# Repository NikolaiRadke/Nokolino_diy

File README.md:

The ATtiny-based litte brother of Noko. This is the Repository for the **diy - Do It Yourself** version. Tiny and cute. And everyone is invited to **contribute**. Nokolino is for everyone. Are you looking for the new PCB version? Look here: [Nokolino_pcb](https://github.com/NikolaiRadke/Nokolino_pcb), or are you an owner of a kit? Look [here](http://github.com/NikolaiRadke/Nokolino).  

> [!NOTE]
> This Repository is not maintained anymore. 
  
What's new? See the [newsblog](https://github.com/NikolaiRadke/Nokolino_diy/tree/master/NEWS.md).   

Like his big brother **Noko**, the little Nokolino delights it's surroundings with cheeky comments. But unlike Noko he is more obstinate - no radio, no display, no frills. Instead of an Arduino he has a small **ATtiny** microcontroller, only an on-off switch and a big button. But he is small, can stay active for days and is, in contrast to his big brother, very easy to build.  
  
Another useful application option would be to use the hardware without the monster suit as a **music box** in an old used doll to bring it back to modern days, maybe with other sounds or songs.  

What does he to - technically? Whenever you press his button, he will laugh. And when he's just turned on, he says something random randomly every statistically 10 minutes. That's ist. Quiet a lot for a stuffed monster!  
  
**Nokolino** stands for **No**ra and Ni**ko**s monster - the appendix **lino** describes the small version.  
  
### Notes for non-German Nokolino makers  
  
Right now, the building wiki, the voice set and the manual are in German. I'll try to translate the wiki and the manual on day. Until then, feel free to ask me for translation, if you need help. **Contribute!** I need an English voice set and English text files. In addition, any other language is welcome, Nokolino is to be cosmopolitan!
  
### Prerequisites
  
Nokolino needs Arduino IDE 1.6.6 or newer (https://www.arduino.cc/en/Main/Software). Copy the folder `Nokolino_diy/src/Nokolino/` into your sketch folder and install ATtiny support. See [how to compile](https://github.com/NikolaiRadke/Nokolino_diy/tree/master/howto_compile) for further instructions. 
  
### Content

```
Nokolino_diy/
├── howto_compile/
|   Manual how compile the sketches in your Arduino IDE and precompiled sketched  
|   └── precompiled/
|       Precompiled hex files
|       ├── ATtiny45/
|       |   Version for the ATtiny45.
|       └── ATtiny85/
|           Version for the ATtiny85.
|
├── linux_uploader/
|   Tool for uploading MP3-files to the JQ6500.
|
├── manual/
|   Nokolino manual in PDF format and a template for a packaging design.
|   └── scribus/
|       Source documents for Scribus with all illustrations and fonts.
|
├── mp3/
|   Voice set for Nokolino/Nokolina in German. English needed? Contribute!
|   ├── female/
|   |   Female voice for Nokolina.
|   |   ├── mp3_16MBit/
|   |   |   Voice set for the 2MB-JQ6500.
|   |   └── mp3_32MBit/
|   |       Enhanced voice set for the 4MB-JQ6500. 
|   └── male/
|       Male voice for Nokolino.
|       ├── mp3_8MBit/
|       |   Low qualitiy files for the 1MB-JQ6500.
|       ├── mp3_16MBit/
|       |   Voice set for the 2MB-JQ6500.
|       └── mp3_32MBit/
|           Enhanched voice set for the 4MB-JQ6500.  
|
├── schematics/
|   The schematics for the Nokolino parts, the Nokolino sewing pattern and shopping list.
|   └── geda/
|       Source documents for gEDA.
|
└── src/
    ATtiny sketch
    └── Nokolino/
        One file, no libraries, no frills. Just Nokolino. 
```
### Let's get started!

Interested in Nokolino? Great! Let's start here: [German wiki](https://github.com/NikolaiRadke/Nokolino_diy/wiki).  
English wiki will follow. One day...

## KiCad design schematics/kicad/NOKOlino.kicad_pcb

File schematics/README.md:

# Schematics

### Technical schematics
* **Nokolino.png**:  
NOKOlino's main schematic. It was written with [gEDA](http://www.geda-project.org/).  
* **Nokolino_phototransistor.png**:  
Optional light sensor extension schematic.  

### Other manuals

* **Nokolino_Pattern.pdf**:
NOKOs sewing pattern. 
* **Nokolino_Einkaufsliste.pdf**:
Shopping list in German.

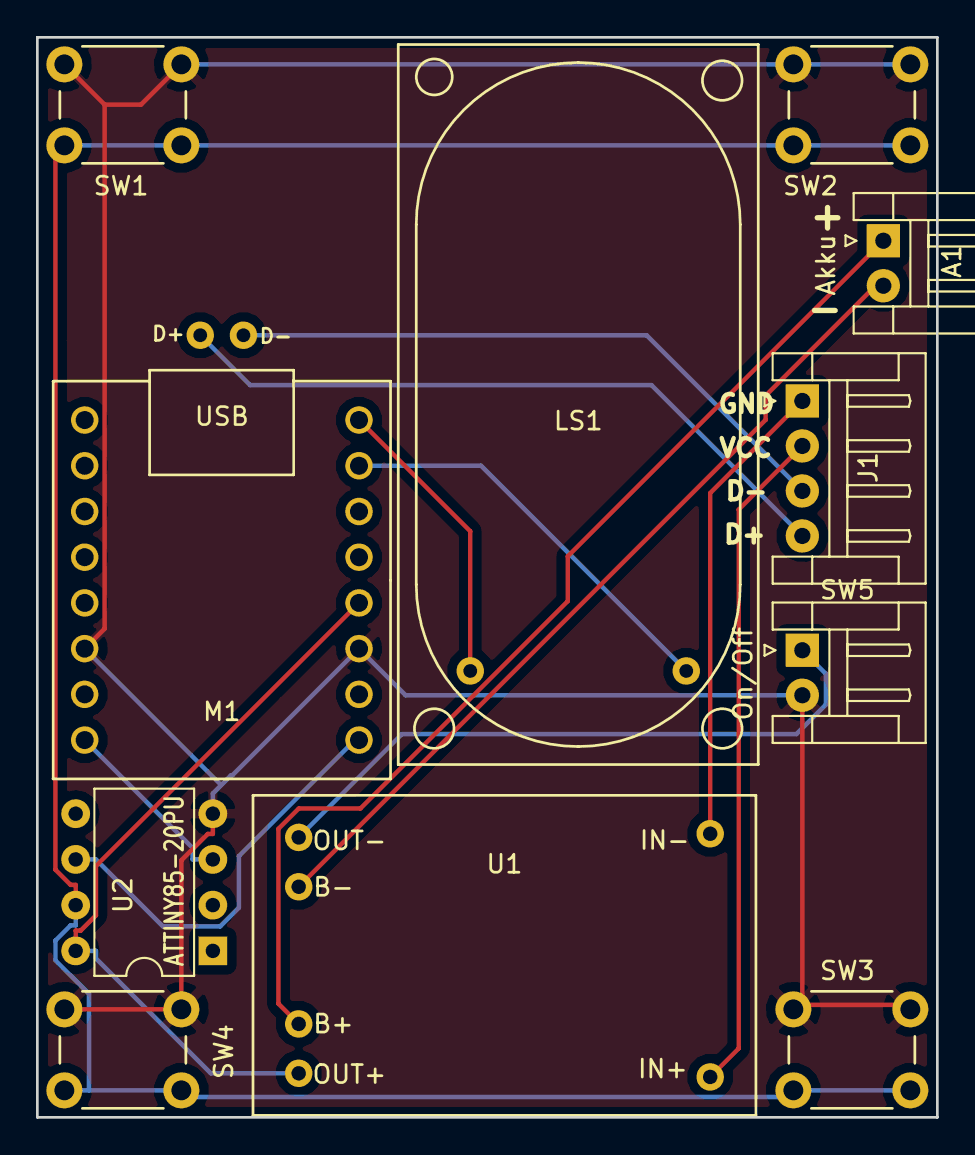
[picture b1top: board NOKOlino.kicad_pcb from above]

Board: 2 copper layers, 50.0 x 60.0 mm, 11 parts (0 on the bottom side), 14 nets.

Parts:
A1: Akku; JST_EH_S02B-EH_02x2.50mm_Angled
J1: USB; JST_EH_S04B-EH_04x2.50mm_Angled
LS1: Speaker; K20.40
M1: JQ6500; JQ6500-16p
SW1: SW1; SW_PUSH_6mm_h13mm
SW2: SW2; SW_PUSH_6mm_h13mm
SW3: SW3; SW_PUSH_6mm_h13mm
SW4: SW4; SW_PUSH_6mm_h13mm
SW5: On/Off; JST_EH_S02B-EH_02x2.50mm_Angled
U1: TP4056; TP4056-Protect
U2: ATTINY85-20PU; DIP-8_W7.62mm

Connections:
D+: J1.4, M1.18
D-: J1.3, M1.17
GND: M1.6, M1.11, SW1.1, SW2.1, SW3.1, SW4.1, SW5.2, U2.4
unnamed: A1.1, U1.4
unnamed: A1.2, U1.5
unnamed: J1.1, U1.2
unnamed: J1.2, U1.1
unnamed: LS1.1, M1.16
unnamed: LS1.2, M1.15
unnamed: M1.8, U2.3
unnamed: M1.9, U2.6
unnamed: SW1.2, SW2.2, SW3.2, SW4.2, U2.7
unnamed: SW5.1, U1.6
VCC: M1.12, U1.3, U2.8

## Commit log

2017-02-13 First upload
2017-02-14 New mp3 and upload tool
2017-02-15 New source directory
2017-02-15 Added schematic
2017-02-27 Huge rework!
2017-02-28 Renamed sketch
2017-03-01 Removed junk
2017-03-01 Cleanup
2017-03-04 Code cleanup
2017-03-05 Huge rework
2017-03-07 Added precompiled .hex files
2017-03-15 Better busy control
2017-03-19 Added deadlock check and ATtiny45 support
2017-03-24 Added new lerning sketch and a german manual
2017-03-28 Updated schematics
2017-03-31 Slightly improved power save mode
2017-04-02 NOKOlino now supports permanent pressed button
2017-04-09 Small code cleanup
2017-12-29 Set .gitattributes
2017-12-29 Set licence
2017-12-29 Added manual fonts
2017-12-31 Some cosmetical fixes
2018-01-01 Added sewing pattern
2018-01-02 Updated linux uploader
2018-01-03 Added German shopping list
2018-01-03 Added new precompiled firmwares
2018-01-04 Updated shopping list
2018-01-05 New firmware 050118
2018-01-05 Added new precompiled hex files
2018-01-08 Update NOKOlino.ino
    Prevents problems when increasing button events
2018-01-09 Firmware V1.0-090118
2018-01-09 Added precompiled firmware 090118
2018-01-09 Small corrections
2018-01-10 Firmware 1.0-100118
2018-01-10 New precompiled firmware
2018-01-13 Added enhanced voice set support
2018-01-13 Removed one obsolete MP3
2018-01-15 Started kicad pcb design
2018-01-15 kicad - circuit done
2018-01-15 kicad - circuit done 2
2018-01-15 kicad - first PCB draft done
2018-01-15 kicad - added first Gerber files and circuit PDF
2018-01-15 kicad - added correct JQ6500 footprint
2018-01-15 kicad - almost finished PCB, added 3D image
2018-01-16 kicad - 50x50mm Version, bitte Schaltplan (Ausgabe.pdf) überprüfen
2018-01-16 kicad - slight changes in JQ6500 part, added NOKO Logo
2018-01-16 kicad - created new Gerber files
2018-01-16 removed old 3D file
2018-01-16 rotated logo
2018-01-18 Lautsprecherfootprint und JST EH gewinkelte Stecker
2018-01-18 removed old file
2018-01-20 Neueste Updates für die Diskussion in #6
    - MP3 Modul nach unten verschoben, so das möglichst viel Platz für einen
    USB Stecker ist
    - Befestigungslöcher des Lautsprechers entfernt
    - Die schematics/kicad/PDF/NOKOlino_PCB.pdf Datei ist ein
    (maßstabsgerechter?) Ausdruck der Leiterplatte, zum Ausprobieren der
    Größenverhältnisse, bitte mal testen, ob das alles so passt.
2018-01-21 NOKOlino logo added to library and board
2018-01-21 Neues PCB für die obere Platte
    - neues PCB angelegt (im Verzeichnis schematics/kicad_top_pcb. Dort sind
    Löcher zur Befestigung des Lautsprechers und Aussparungen für den
    Schallaustritt vorgesehen. Die Schlitze sind 1mm breit und haben 0,6mm
    Abstand - gibt es dagegen Einwände? Oder bessere Ideen?
    - Wegen besserer Stabilität mit Kupferflächen auf beiden Seiten
    - NOKOlino Logo kommt noch rauf
2018-01-26 New firmware 1.0-280118
2018-01-27 New firmware 1.0-270118
2018-01-27 breitere Schlitze und Stege
2018-01-28 last changes, directories cleaned up
2018-01-28 added logo, created new 3D renders
2018-01-28 last changes, added fake pads to top PCB for drill file generation
2018-01-28 last changes
2018-01-28 noch mehr last changes
2018-01-30 some file and directory structure cleanup and more pictures
2018-02-16 Fooprint of MP3 module corrected
2018-02-16 Ever so slight correction footprint of TP module
2018-02-18 removed ref*** labels
2018-02-19 Create Gerber files
2018-03-08 Fixed flash tool for 32MBit modules
2018-03-12 Lautsprecher Zeichnung auf die Unterseite gerückt, nur die Oberseite hat jetzt das Logo und den Namen, ref*** ist beseitigt
2018-03-12 Gerber Zip File geupdated
2018-03-12 Firmware 120318
2018-03-12 Repro cleanup
2018-03-13 Akku Anschluss nach links gerückt
2018-03-13 USB und Schalter zusammen, Akku Label zurecht gerückt
2018-03-13 NOKOlino_Gerbers.zip geupdated
2018-03-14 Added Flash tool ISO for poor Windows user
2018-03-15 Added Images to repair JQ6500 modules without onboard software
2018-03-15 Added new precompiled sketches
2018-03-15 Edited image for stupid Joilet utf-16 encoding
2018-03-15 New UEFI/BIOS compatible image with easy frontend
2018-03-16 Schon wieder letzte Änderungen
2018-03-17 Repository cleanup
2018-05-01 Beschriftung der Anschlüsse berichtigt
2018-05-01 GERBER files erstellt und ZIP geupdated
2018-05-03 Enlarged solder pads
2018-05-03 GERBER files created and ZIP archive updated
2018-05-03 Init again
2018-05-03 New gerber files
2018-05-09 New speech set is now preset
2018-05-11 Added female voice set
2018-05-11 Renamed folder
2018-05-15 Updated upload tool
2018-05-15 Updated upload an repair software
2018-05-22 Smoother pattern graphic
2018-05-24 Better data compression for 16MBit set
2018-05-28 Set 16MBit voice set as default
2018-06-29 Improved power saving when battery is low
2018-06-29 Experimental version with phototransitor
2018-07-05 New phototransistor version firmware
2018-08-21 Updated linux upload tool
2018-09-22 New Firmware 220918
2018-09-24 Disabled analog comparator again
2018-09-25 Firmware 250918
2018-10-19 New jq6500 upload tool
2019-01-15 Reworked volume control
2019-04-16 Firmware 160419 - fixed a dark mode bug
2019-08-03 New firmware 2.1-030819
2019-08-04 Clean up
2019-08-05 Schmatic for phototransistor extension
2019-08-27 New linux uploader
2020-06-03 Updated repository
2022-02-04 Added version for Digispark moduke
2026-04-12 Update README to reflect repository maintenance status
    Added a note indicating that the repository is no longer maintained.
